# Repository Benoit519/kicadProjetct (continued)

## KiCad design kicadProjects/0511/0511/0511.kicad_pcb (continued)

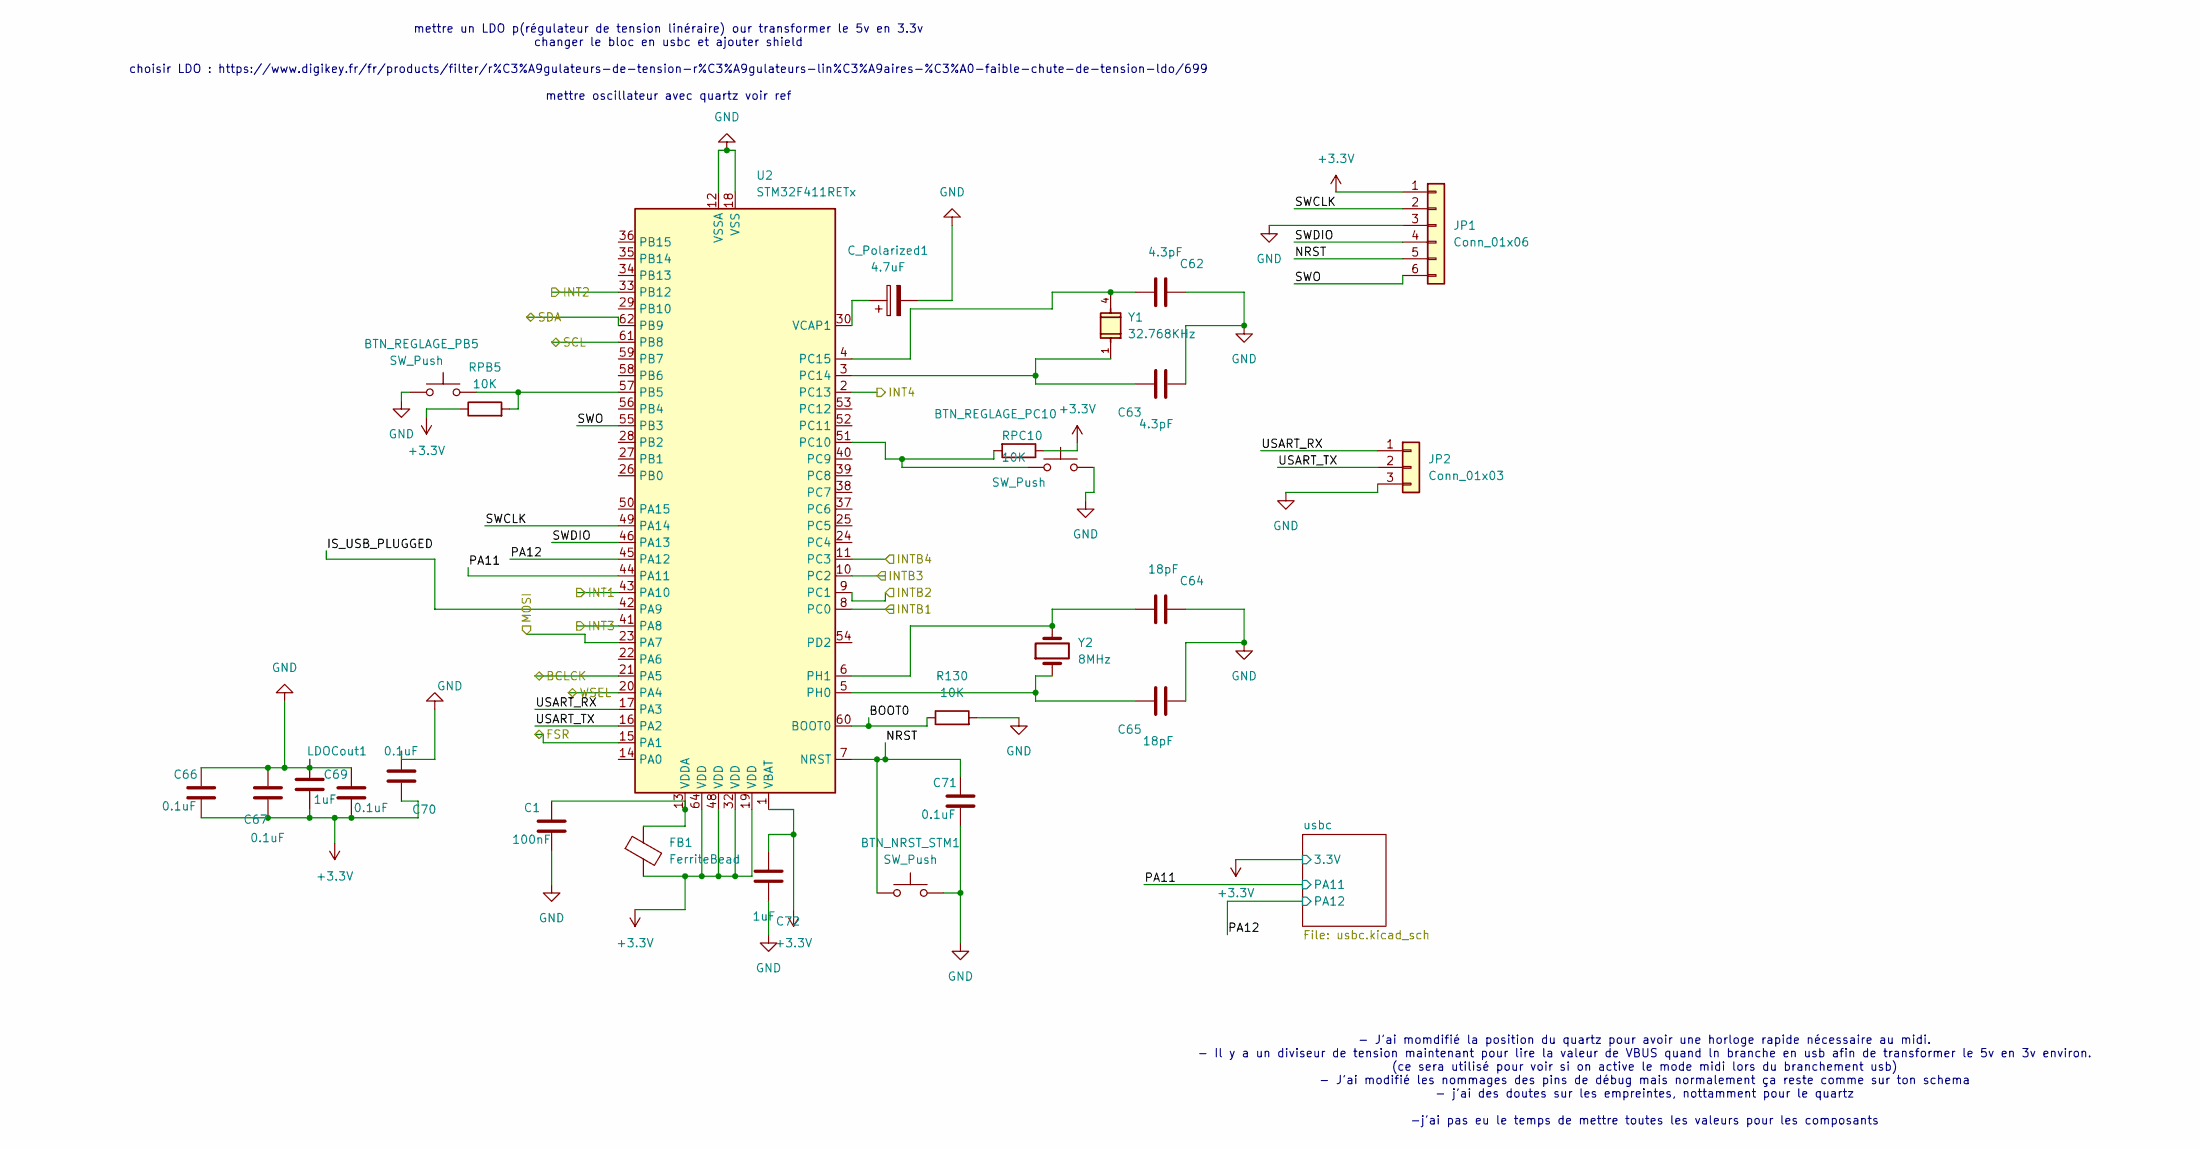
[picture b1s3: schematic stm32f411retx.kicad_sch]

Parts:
BTN_NRST_STM1: SW_Push; SW_SPST_TL3342
BTN_REGLAGE_PB5: SW_Push; SW_SPST_TL3342
BTN_REGLAGE_PC10: SW_Push; SW_SPST_TL3342
C1: 100nF; C_0603_1608Metric
C62, C63: 4.3pF; C_0603_1608Metric
C64, C65: 18pF; C_0603_1608Metric
C66, C67, C69, C70, C71: 0.1uF; C_0603_1608Metric
C72: 1uF; C_0603_1608Metric
C_Polarized1: 4.7uF; CP_EIA-6032-28_Kemet-C
FB1: FerriteBead; L_0603_1608Metric
JP1: Conn_01x06; PinSocket_1x06_P2.54mm_Vertical
JP2: Conn_01x03; PinSocket_1x03_P2.54mm_Vertical
LDOCout1: 1uF; C_0603_1608Metric
R130: 10K; R_0603_1608Metric
RPB5: 10K; R_0603_1608Metric
RPC10: 10K; R_0603_1608Metric
U2: STM32F411RETx; LQFP-64_10x10mm_P0.5mm
Y1: 32.768KHz; XTAL_ABS25-32.768KHZ-6-T; DigiKey_Part_Number 535-10240-1-ND
Y2: 8MHz; XTAL_ABLS2-8.000MHZ-D4Y-T

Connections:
+3.3V: C66.2, C67.2, C69.2, C70.2, C72.1, FB1.2, JP1.1, LDOCout1.2, RPB5.1, RPC10.1, U2.1 (VBAT), U2.19 (VDD), U2.32 (VDD), U2.48 (VDD), U2.64 (VDD); also elsewhere on the board
/BCLCK: U2.21 (PA5); also elsewhere on the board
/FSR: U2.15 (PA1); also elsewhere on the board
/INT1: U2.43 (PA10); also elsewhere on the board
/INT2: U2.33 (PB12); also elsewhere on the board
/INT3: U2.41 (PA8); also elsewhere on the board
/INT4: U2.2 (PC13); also elsewhere on the board
/INTB1: U2.8 (PC0); also elsewhere on the board
/INTB2: U2.9 (PC1); also elsewhere on the board
/INTB3: U2.10 (PC2); also elsewhere on the board
/INTB4: U2.11 (PC3); also elsewhere on the board
/MOSI: U2.23 (PA7); also elsewhere on the board
/SCL: U2.61 (PB8); also elsewhere on the board
/SDA: U2.62 (PB9); also elsewhere on the board
/Stm32f411retx/BOOT0: R130.1, U2.60 (BOOT0)
/Stm32f411retx/IS_USB_PLUGGED: U2.42 (PA9)
/Stm32f411retx/NRST: BTN_NRST_STM1.1, C71.1, JP1.5, U2.7 (NRST)
/Stm32f411retx/PA11: U2.44 (PA11); also elsewhere on the board
/Stm32f411retx/PA12: U2.45 (PA12); also elsewhere on the board
/Stm32f411retx/SWCLK: JP1.2, U2.49 (PA14)
/Stm32f411retx/SWDIO: JP1.4, U2.46 (PA13)
/Stm32f411retx/SWO: JP1.6, U2.55 (PB3)
/Stm32f411retx/USART_RX: JP2.1, U2.17 (PA3)
/Stm32f411retx/USART_TX: JP2.2, U2.16 (PA2)
/WSEL: U2.20 (PA4); also elsewhere on the board
GND: BTN_NRST_STM1.2, BTN_REGLAGE_PB5.1, BTN_REGLAGE_PC10.2, C1.2, C62.1, C63.2, C64.1, C65.2, C66.1, C67.1, C69.1, C70.1, C71.2, C72.2, C_Polarized1.2, JP1.3, JP2.3, LDOCout1.1, R130.2, U2.12 (VSSA), U2.18 (VSS), U2.31 (VSS), U2.47 (VSS), U2.63 (VSS); also elsewhere on the board
unnamed: BTN_REGLAGE_PB5.2, RPB5.2, U2.57 (PB5)
unnamed: BTN_REGLAGE_PC10.1, RPC10.2, U2.51 (PC10)
unnamed: C63.1, U2.3 (PC14), Y1.1
unnamed: C62.2, U2.4 (PC15), Y1.4
unnamed: C65.1, U2.5 (PH0), Y2.1
unnamed: C64.2, U2.6 (PH1), Y2.2
unnamed: C_Polarized1.1, U2.30 (VCAP1)
unnamed: C1.1, FB1.1, U2.13 (VDDA)

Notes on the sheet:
- J'ai momdifié la position du quartz pour avoir une horloge rapide nécessaire au midi. - Il y a un diviseur de tension maintenant pour lire la valeur de VBUS quand ln branche en usb afin de transformer le 5v en 3v environ. (ce sera utilisé pour voir si on active le mode midi lors du branchement us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
mettre un LDO p(régulateur de tension linéraire) our transformer le 5v en 3.3v changer le bloc en usbc et ajouter shield choisir LDO : https://www.digikey.fr/fr/products/filter/r%C3%A9gulateurs-de-tension-r%C3%A9gulateurs-lin%C3%A9aires-%C3%A0-faible-chute-de-tension-ldo/699 mettre oscillateur avec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

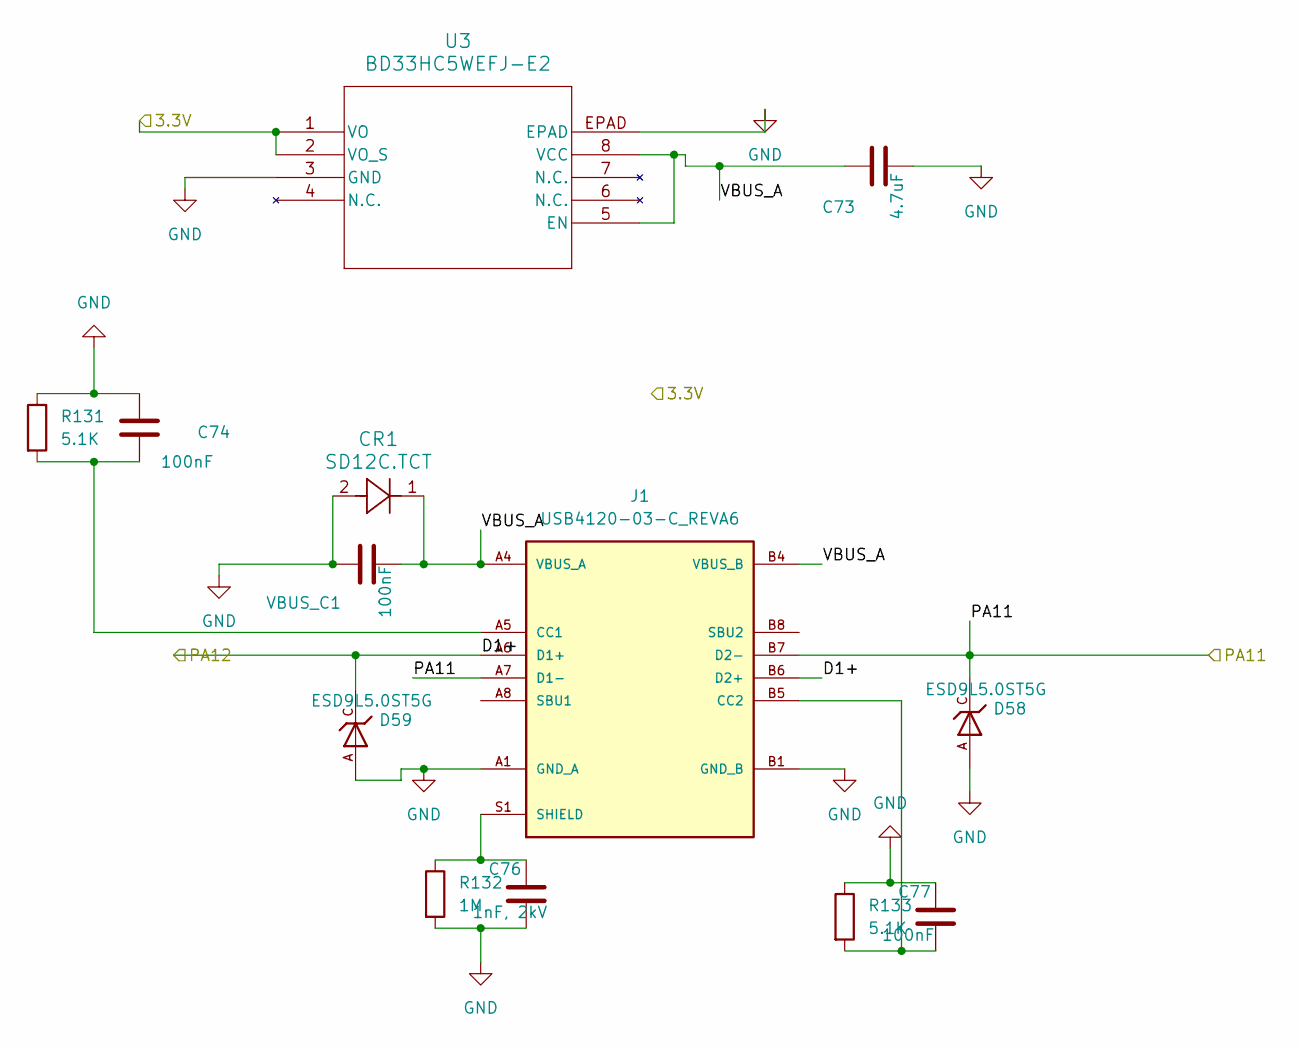
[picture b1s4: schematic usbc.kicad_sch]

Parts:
C73: 4.7uF; C_0603_1608Metric
C74, C77: 100nF; C_0603_1608Metric
C76: 1nF, 2kV; C_0603_1608Metric
CR1: SD12C.TCT; CR_SD05_SEM
D58, D59: ESD9L5.0ST5G; DIOM1006X40N; PARTREV 7; DigiKey_Part_Number ESD9L5.0ST5GOSCT-ND
J1: USB4120-03-C_REVA6; GCT_USB4120-03-C_REVA6; PARTREV A6; DigiKey_Part_Number 2073-USB4120-03-CCT-ND
R131, R133: 5.1K; R_0603_1608Metric
R132: 1M; R_0603_1608Metric
U3: BD33HC5WEFJ-E2; HTSOP-J8_ROM
VBUS_C1: 100nF; C_0603_1608Metric

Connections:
+3.3V: U3.1 (VO), U3.2 (VO_S); also elsewhere on the board
/Stm32f411retx/PA11: D58.C, J1.A7 (D1-), J1.B7 (D2-); also elsewhere on the board
/Stm32f411retx/PA12: D59.C, J1.A6 (D1+), J1.B6 (D2+); also elsewhere on the board
GND: C73.2, C74.1, C76.2, C77.1, CR1.2, D58.A, D59.A, J1.A1 (GND_A), J1.A12 (GND_A), J1.B1 (GND_B), J1.B12 (GND_B), R131.1, R132.2, R133.1, U3.3 (GND), U3.EPAD, VBUS_C1.1; also elsewhere on the board
unnamed: C76.1, J1.S1 (SHIELD), J1.S2 (SHIELD), J1.S3 (SHIELD), J1.S4 (SHIELD), R132.1
unnamed: C74.2, J1.A5 (CC1), R131.2
unnamed: C77.2, J1.B5 (CC2), R133.2
VBUS_A: C73.1, CR1.1, J1.A4 (VBUS_A), J1.A9 (VBUS_A), J1.B4 (VBUS_B), J1.B9 (VBUS_B), U3.5 (EN), U3.8 (VCC), VBUS_C1.2

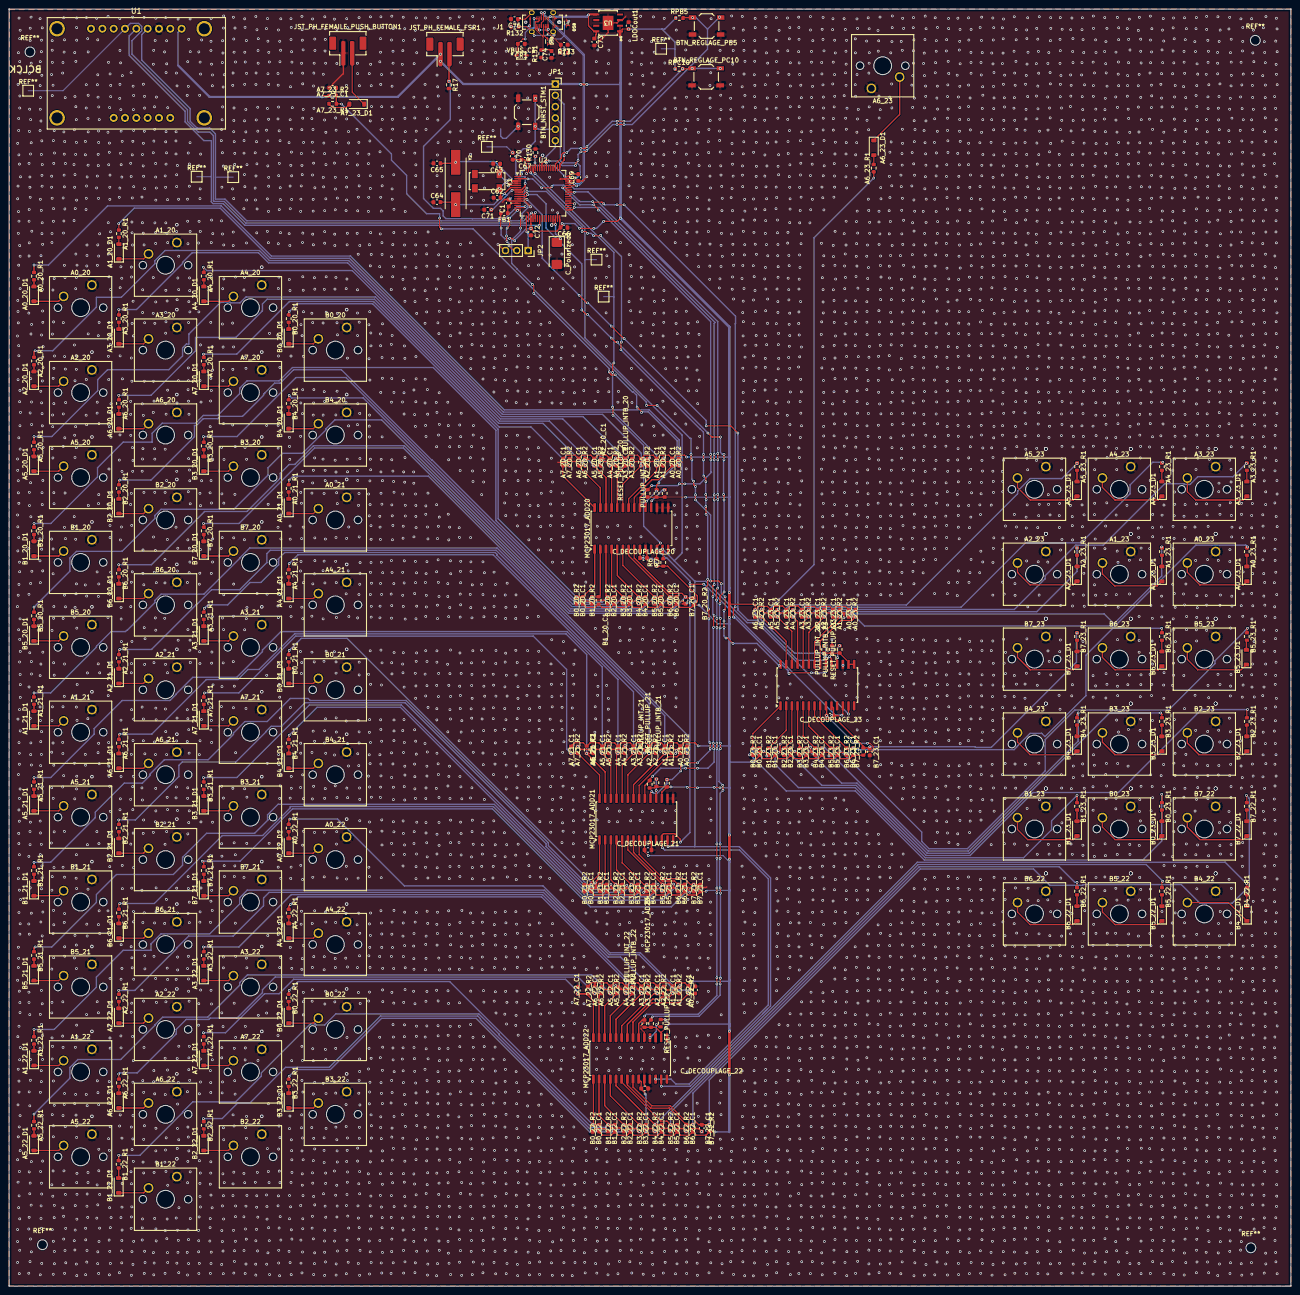
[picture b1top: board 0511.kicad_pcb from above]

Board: 2 copper layers, 287.6 x 286.5 mm, 383 parts (0 on the bottom side), 233 nets.

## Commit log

2025-11-10 test
2025-11-10 ajout kicad project
2025-11-10 ajout empreintes
2025-11-10 ajout empreinte sm32 black pill
2025-11-10 corrections empreintes mcp23017
2025-11-11 poursuite schema
2025-11-11 poursuite
2025-11-13 rectifications, modif empreinte capteur fsr, correctifs warnings
2025-11-20 ajout feuille hiérarchique
2025-11-20 correctifs connections mcp23017
2025-11-22 ajout 2 mcp23017
2025-11-22 ajout librairie projet
2025-11-24 correctifs connexions manquantes
2025-11-25 ajout connexions manquantes
2025-11-25 overriden pcb file
2025-12-16 adaptation empreintes mcp23017 ajout valeurs aux résistances corrections empreintes des résistances et condensateurs
2025-12-19 deleted files
2026-01-06 updated backups
2026-01-07 started alim bloc
2026-01-07 started stm32 hierarchical b=view scheme
2026-01-09 stm32 bloc implementation
2026-01-09 started to add hierarchical pins
2026-01-09 assignation empreintes
2026-01-09 added comments
2026-01-10 add values
2026-01-11 imported compoents
2026-01-12 added LDO, quartz, usb c
2026-01-12 started to annotate and place buttons on pcb
2026-01-12 ended place right hand buttons
2026-01-16 poursuite placement et nommage références
2026-01-16 poursuite annotaion circuits rdc
2026-01-16 fin annotation bouttons
2026-01-16 fin placement mcp23017 addresse 20
2026-01-20 placed left hand buttons
2026-01-30 added script to place components
2026-01-30 poursuite placement
2026-01-30 ajout script plan de masse
2026-01-31 Revert "ajout script plan de masse"
    This reverts commit 7d1af92af7d1ea82f80810c5c48bcbfb97ed7daa.
2026-02-02 placement composants
2026-02-03 ajouut ferrite
2026-02-03 updated initial positions for mcp rcd filters
2026-02-04 ended sript to place buttons
2026-02-04 placed vias gnd
2026-02-04 placed D1 and R1 and for right hand
2026-02-04 placed left hand
2026-02-04 added r1, d1, via on left hand
2026-02-04 updated R2, C1 placement
2026-02-05 ended georaphical placement
2026-02-07 placement en T
2026-02-08 fin placement mcp23017 20
2026-02-09 poursuite routing
2026-02-09 routage par bottom
2026-02-10 début placement main gauche
2026-02-11 fin routage bouttons main gauche
2026-02-11 ended routing left hand
2026-02-11 added connections scl, sda
2026-02-17 placed components around stm32f411rx
2026-02-18 ended pplacement stm32 compoenents
2026-02-19 poursuite placement usb c component
2026-02-24 ajout rail alim
2026-02-26 poursuite alim
2026-03-05 poursuite cablage
2026-03-06 ajout interruptions
2026-03-06 ajout plan de masse top
2026-03-06 ajout gnd bottom
2026-03-06 ajout plan de masse
2026-03-07 ajout script à modifier vias
2026-03-07 correctifs
2026-03-11 added B port interruptions, updated schem and pcb
2026-03-16 ajout empreinte quarty mhz
2026-03-16 correctif adafruit component
2026-03-16 added push buttons
2026-03-18 correctif empreinte, ajout tests points
2026-03-20 ajout trous fixation
2026-03-27 correctifs, ajout sérigraphie test points
2026-03-27 corrected DRC errors
2026-03-27 correction, début mise en place BOM
2026-03-30 correctifs valeurs manquantes
2026-03-30 ajout BOM, correctifs
2026-03-31 corrections
2026-03-31 ajout dossier fabrication
2026-03-31 ajout NM adafruit uda1334a
